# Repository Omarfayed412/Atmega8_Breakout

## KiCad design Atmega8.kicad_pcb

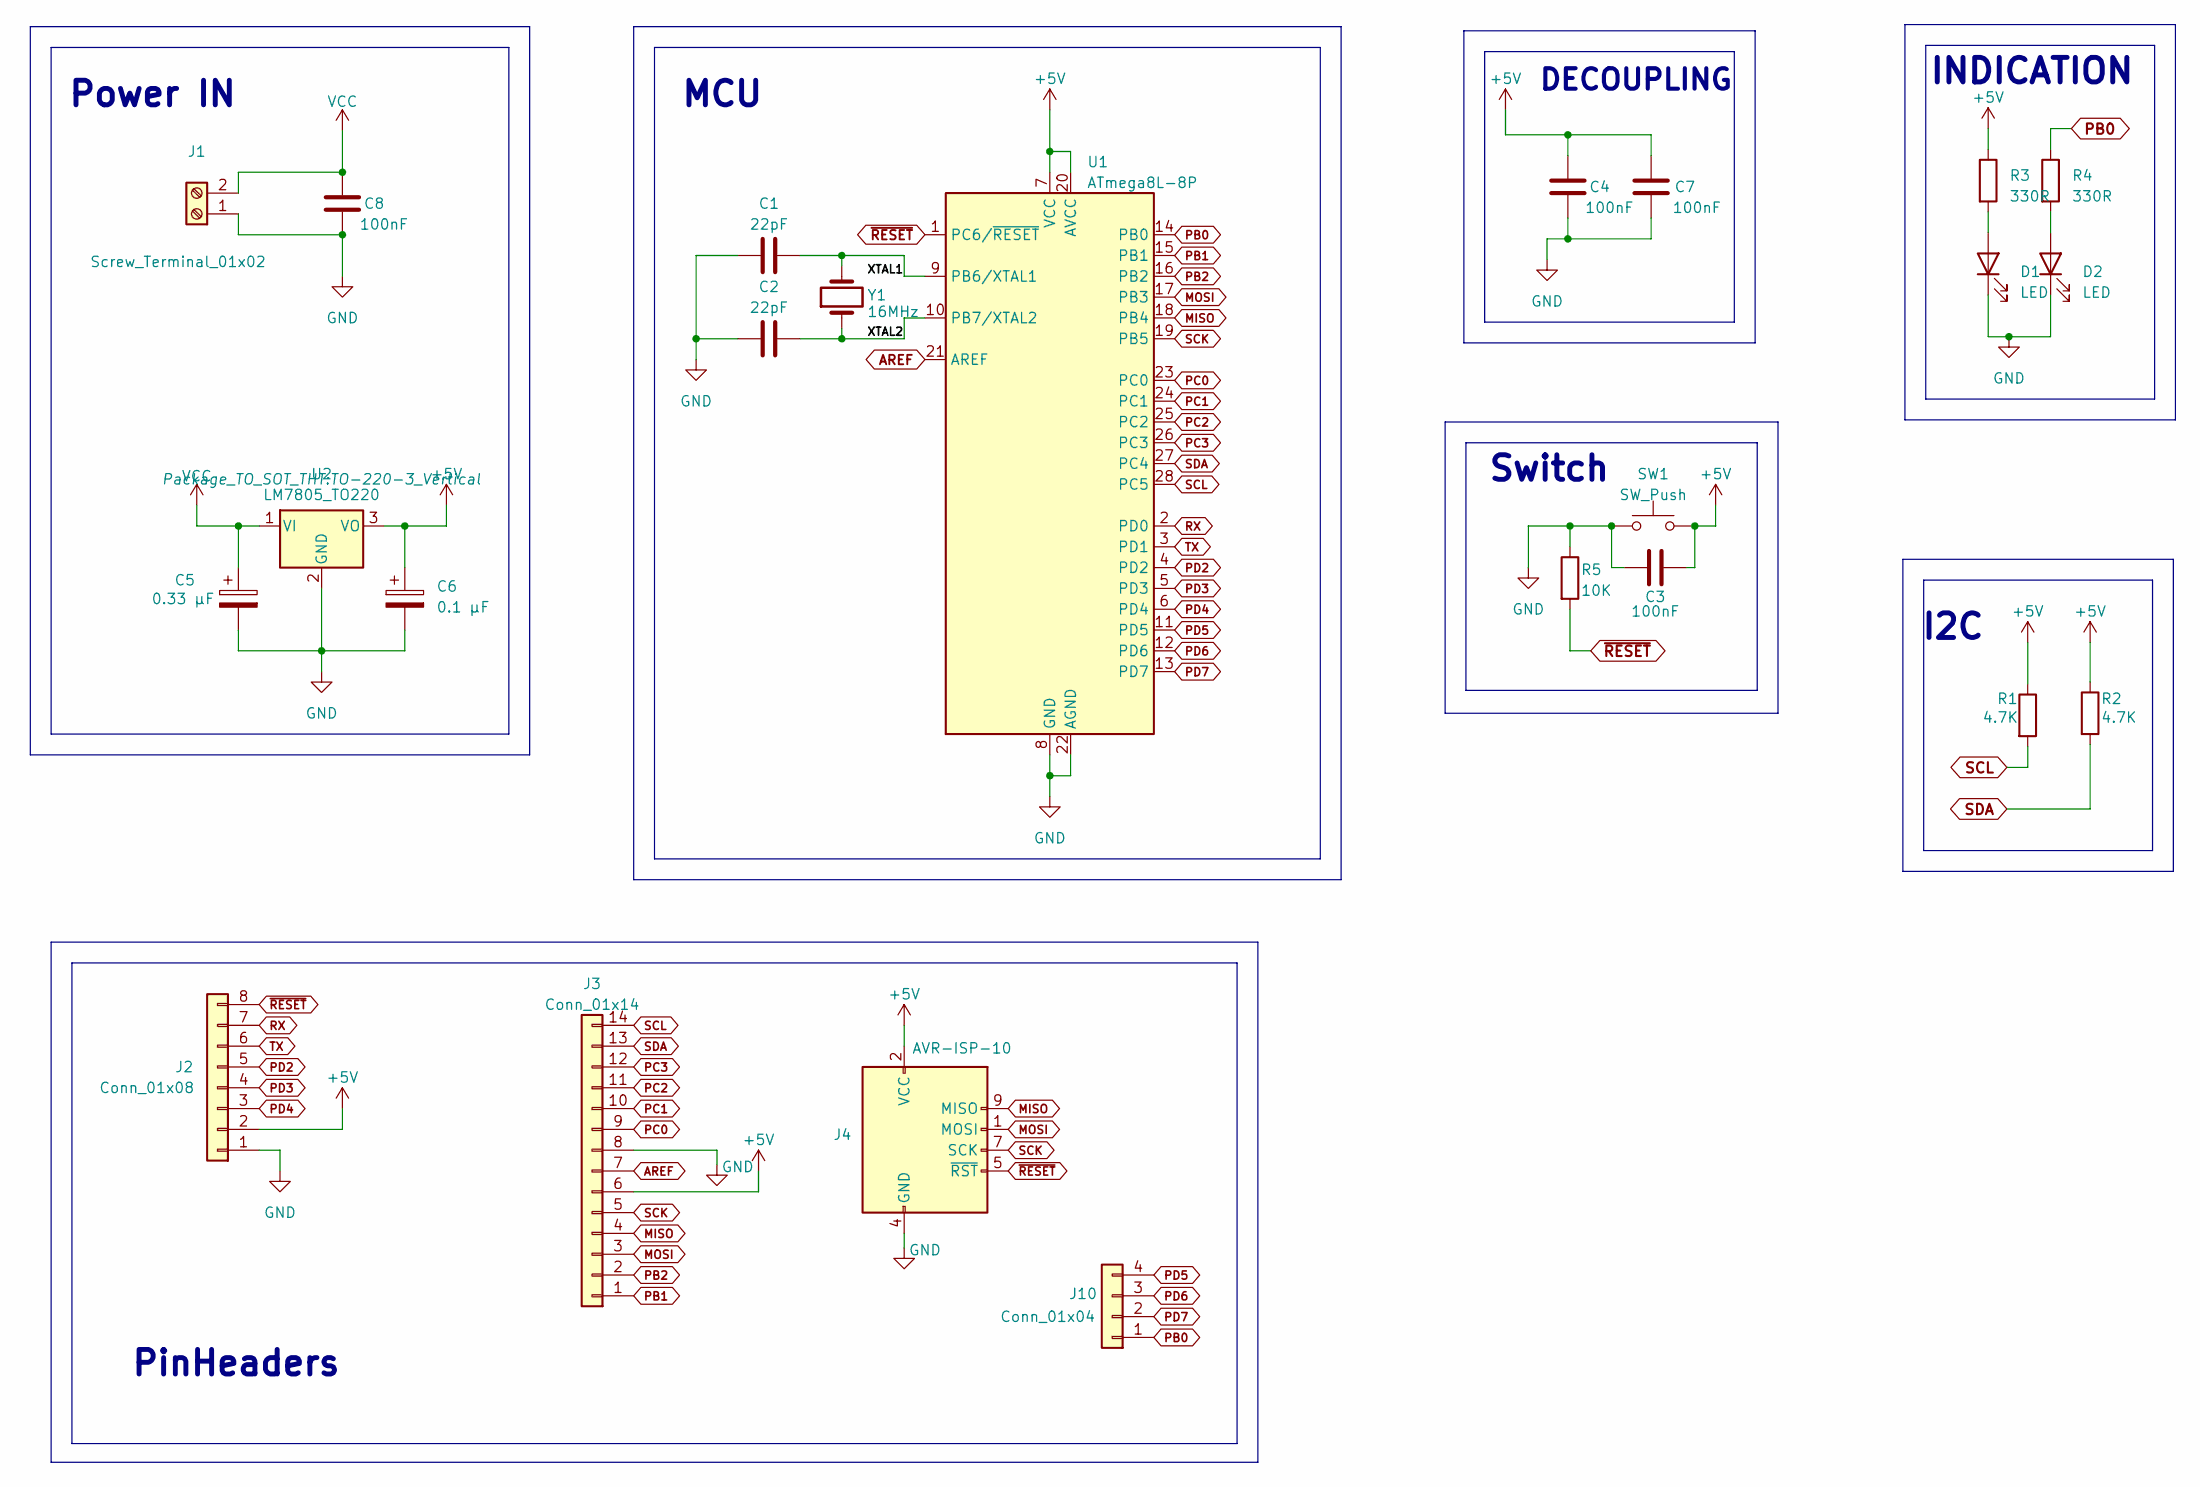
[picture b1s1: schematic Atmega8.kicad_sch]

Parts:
C1, C2: 22pF; C_0805_2012Metric
C3, C4, C7, C8: 100nF; C_0805_2012Metric
C5: 0.33 µF; CP_Radial_D6.3mm_P2.50mm
C6: 0.1 µF; CP_Radial_D6.3mm_P2.50mm
D1, D2: LED; LED_D5.0mm
J1: Screw_Terminal_01x02; TerminalBlock_Phoenix_MKDS-1,5-2-5.08_1x02_P5.08mm_Horizont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
J2: Conn_01x08; PinSocket_1x08_P2.54mm_Vertical
J3: Conn_01x14; PinSocket_1x14_P2.54mm_Vertical
J4: AVR-ISP-10; PinHeader_2x05_P2.54mm_Vertical
J10: Conn_01x04; PinSocket_1x04_P2.54mm_Vertical
R1, R2: 4.7K; R_0805_2012Metric
R3: 330R; R_1206_3216Metric
R4: 330R; R_Axial_DIN0204_L3.6mm_D1.6mm_P5.08mm_Horizontal
R5: 10K; R_Axial_DIN0204_L3.6mm_D1.6mm_P5.08mm_Horizontal
SW1: SW_Push; SW_PUSH_6mm
U1: ATmega8L-8P; DIP-28_W7.62mm
U2: LM7805_TO220; TO-220-3_Vertical
Y1: 16MHz; Crystal_HC18-U_Vertical

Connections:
+5V: C3.2, C4.2, C6.1, C7.2, J2.2, J3.6, J4.2 (VCC), R1.1, R2.1, R3.1, SW1.2, U1.7 (VCC), U1.20 (AVCC), U2.3 (VO)
/XTAL1: C1.2, U1.9 (PB6/XTAL1), Y1.2
/XTAL2: C2.2, U1.10 (PB7/XTAL2), Y1.1
AREF: J3.7, U1.21 (AREF)
GND: C1.1, C2.1, C3.1, C4.1, C5.2, C6.2, C7.1, C8.1, D1.1 (K), D2.1 (K), J1.1, J2.1, J3.8, J4.4 (GND), J4.6 (GND), J4.8 (GND), J4.10 (GND), R5.1, SW1.1, U1.8 (GND), U1.22 (AGND), U2.2 (GND)
MISO: J3.4, J4.9 (MISO), U1.18 (PB4)
MOSI: J3.3, J4.1 (MOSI), U1.17 (PB3)
unnamed: D1.2 (A), R3.2
unnamed: D2.2 (A), R4.2
PB0: J10.1, R4.1, U1.14 (PB0)
PB1: J3.1, U1.15 (PB1)
PB2: J3.2, U1.16 (PB2)
PC0: J3.9, U1.23 (PC0)
PC1: J3.10, U1.24 (PC1)
PC2: J3.11, U1.25 (PC2)
PC3: J3.12, U1.26 (PC3)
PD2: J2.5, U1.4 (PD2)
PD3: J2.4, U1.5 (PD3)
PD4: J2.3, U1.6 (PD4)
PD5: J10.4, U1.11 (PD5)
PD6: J10.3, U1.12 (PD6)
PD7: J10.2, U1.13 (PD7)
RX: J2.7, U1.2 (PD0)
SCK: J3.5, J4.7 (SCK), U1.19 (PB5)
SCL: J3.14, R1.2, U1.28 (PC5)
SDA: J3.13, R2.2, U1.27 (PC4)
TX: J2.6, U1.3 (PD1)
VCC: C5.1, C8.2, J1.2, U2.1 (VI)
~RESET: J2.8, J4.5 (~RST), R5.2, U1.1 (PC6/~RESET)

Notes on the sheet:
DECOUPLING
Switch
Power IN
INDICATION
PinHeaders
MCU
I2C

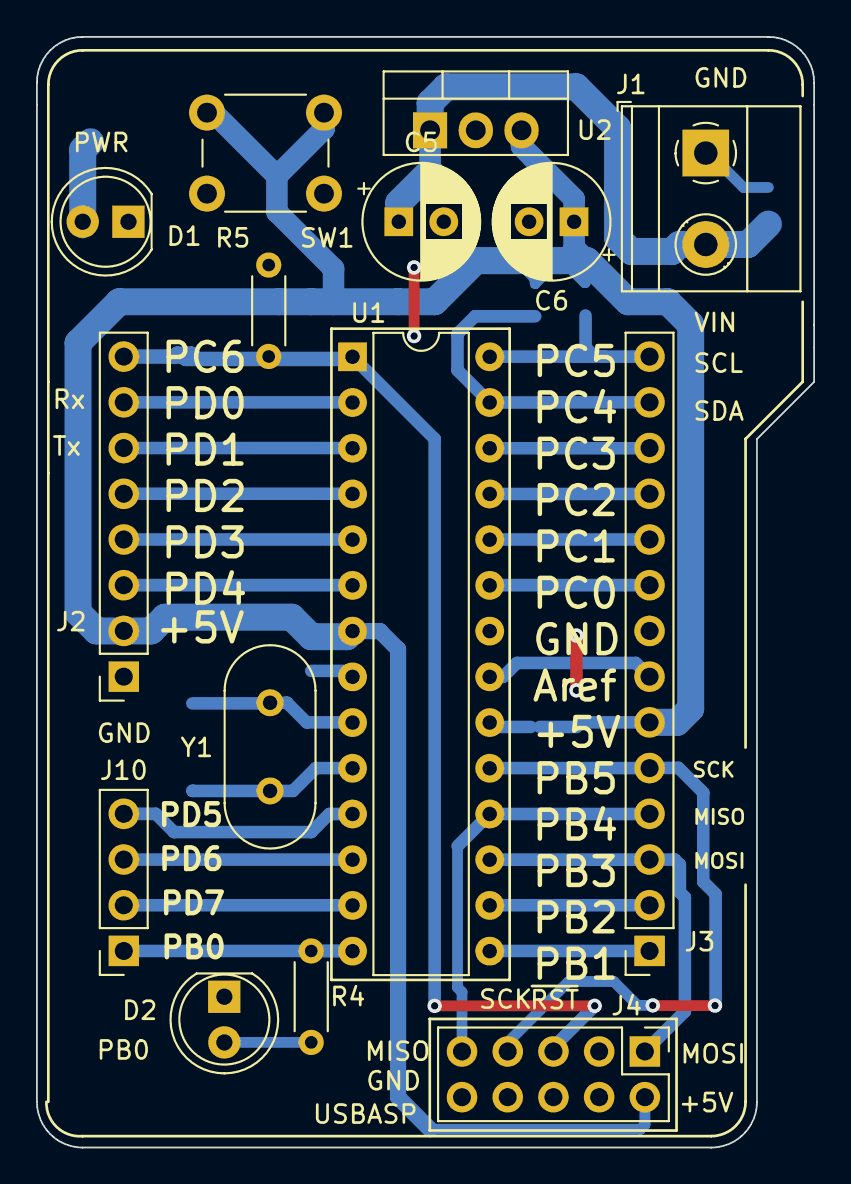
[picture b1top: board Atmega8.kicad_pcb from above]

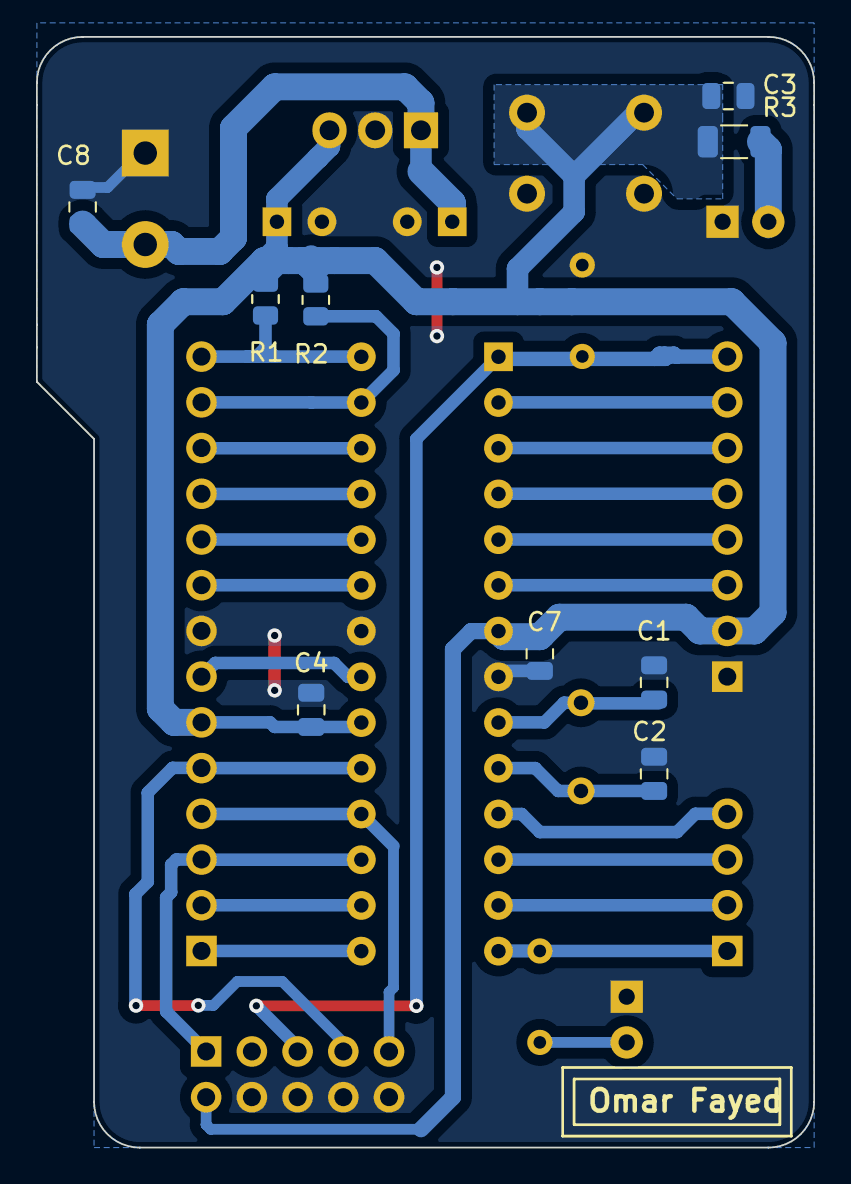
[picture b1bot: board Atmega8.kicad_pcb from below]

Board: 2 copper layers, 43.2 x 61.7 mm, 24 parts (9 on the bottom side), 29 nets.

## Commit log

2023-11-23 Added the design files
